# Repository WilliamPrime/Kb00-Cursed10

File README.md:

This was a shortish project where i wanted to make my own keyboard with my own layout.

The reason for wanting to do this was that i have limited desk space so i prefer a smaller more compact keyboard, so as of currently i use a 65% keyboard
however i do miss having a full size num pad and FN keys so i wanted to create a layout, and keyboard that would focus on getting a full key layout but making it more compact

# some pictures of the project

# BOM

|part    |cost  |notes               |link                                                 |
|--------|------|--------------------|-----------------------------------------------------|
|keycaps |19.97 |                    |https://www.aliexpress.com/item/1005005981079053.html|
|PCB     |43    |JLC!                |                                                     |
|Switches|34.19 |clicky clicky!      |https://www.aliexpress.com/item/1005007779640100.html|
|Diodes  |3.1   |need 2 lots of 1.55 |https://www.aliexpress.com/item/1005006127068810.html|
|PI pico |2.17  |pico with usb type c|https://www.aliexpress.com/item/1005003753933847.html|
|PLA     |0     |using my own        |                                                     |
|Sum     |111.61|                    |                                                     |

total cost $102.43

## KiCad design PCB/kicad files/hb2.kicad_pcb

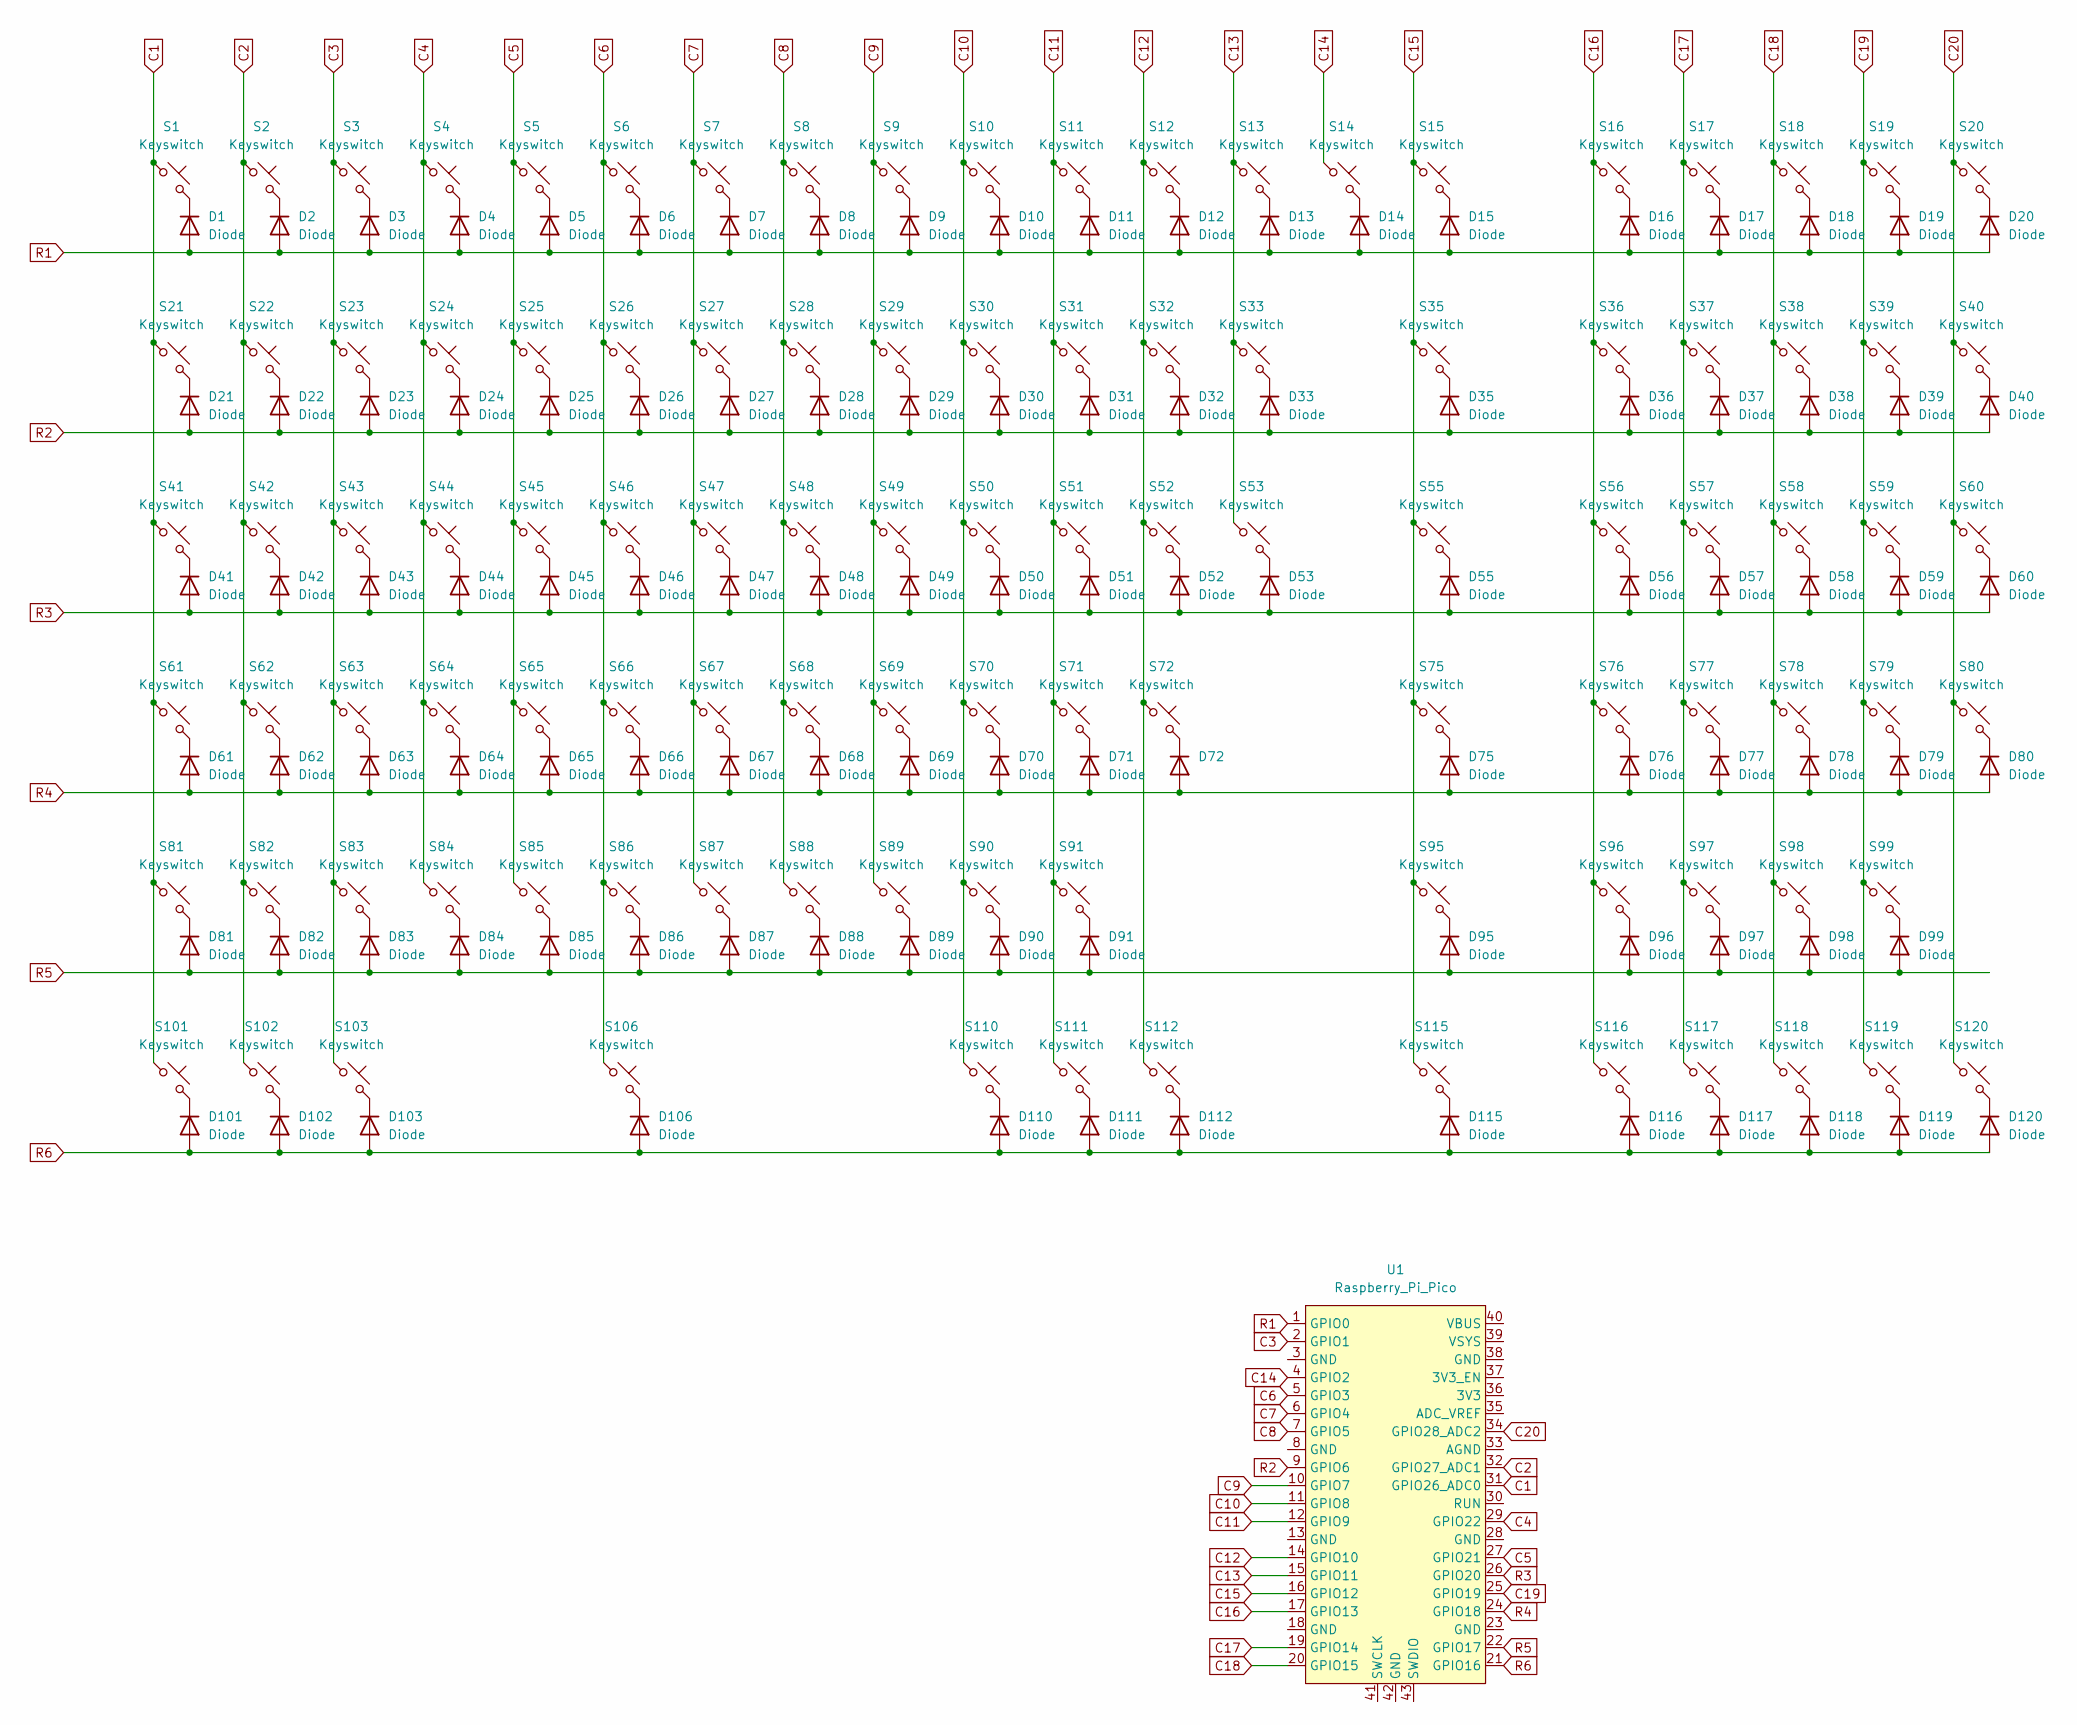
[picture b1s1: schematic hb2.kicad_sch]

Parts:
D1, D2, D3, D4, D5, D6, D7, D8, D9, D10, D11, D12, D13, D14, D15, D16, D17, D18, D19, D20, D21, D22, D23, D24, D25, D26, D27, D28, D29, D30, D31, D32, D33, D35, D36, D37, D38, D39, D40, D41, D42, D43, D44, D45, D46, D47, D48, D49, D50, D51, D52, D53, D55, D56, D57, D58, D59, D60, D61, D62, D63, D64, D65, D66, D67, D68, D69, D70, D71, D72, D75, D76, D77, D78, D79, D80, D81, D82, D83, D84, D85, D86, D87, D88, D89, D90, D91, D95, D96, D97, D98, D99, D101, D102, D103, D106, D110, D111, D112, D115, D116, D117, D118, D119, D120: Diode; D_DO-35_SOD27_P7.62mm_Horizontal
S1, S2, S3, S4, S5, S6, S7, S8, S9, S10, S11, S12, S13, S14, S15, S16, S17, S18, S19, S20, S21, S22, S23, S24, S25, S26, S27, S28, S29, S30, S31, S32, S33, S35, S36, S37, S38, S39, S40, S41, S42, S43, S44, S45, S46, S47, S48, S49, S50, S51, S52, S53, S55, S56, S57, S58, S59, S60, S61, S62, S63, S64, S65, S66, S67, S68, S69, S70, S71, S72, S75, S76, S77, S78, S79, S80, S81, S82, S83, S84, S85, S86, S87, S88, S89, S90, S91, S95, S96, S97, S98, S99, S101, S102, S103, S106, S110, S111, S112, S115, S116, S117, S118, S119, S120: Keyswitch; SW_Cherry_MX_PCB_1.00u
U1: Raspberry_Pi_Pico

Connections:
C1: S1.1, S21.1, S41.1, S61.1, S81.1, S101.1, U1.31 (GPIO26_ADC0)
C2: S2.1, S22.1, S42.1, S62.1, S82.1, S102.1, U1.32 (GPIO27_ADC1)
C3: S3.1, S23.1, S43.1, S63.1, S83.1, S103.1, U1.2 (GPIO1)
C4: S4.1, S24.1, S44.1, S64.1, S84.1, U1.29 (GPIO22)
C5: S5.1, S25.1, S45.1, S65.1, S85.1, U1.27 (GPIO21)
C6: S6.1, S26.1, S46.1, S66.1, S86.1, S106.1, U1.5 (GPIO3)
C7: S7.1, S27.1, S47.1, S67.1, S87.1, U1.6 (GPIO4)
C8: S8.1, S28.1, S48.1, S68.1, S88.1, U1.7 (GPIO5)
C9: S9.1, S29.1, S49.1, S69.1, S89.1, U1.10 (GPIO7)
C10: S10.1, S30.1, S50.1, S70.1, S90.1, S110.1, U1.11 (GPIO8)
C11: S11.1, S31.1, S51.1, S71.1, S91.1, S111.1, U1.12 (GPIO9)
C12: S12.1, S32.1, S52.1, S72.1, S112.1, U1.14 (GPIO10)
C13: S13.1, S33.1, S53.1, U1.15 (GPIO11)
C14: S14.1, U1.4 (GPIO2)
C15: S15.1, S35.1, S55.1, S75.1, S95.1, S115.1, U1.16 (GPIO12)
C16: S16.1, S36.1, S56.1, S76.1, S96.1, S116.1, U1.17 (GPIO13)
C17: S17.1, S37.1, S57.1, S77.1, S97.1, S117.1, U1.19 (GPIO14)
C18: S18.1, S38.1, S58.1, S78.1, S98.1, S118.1, U1.20 (GPIO15)
C19: S19.1, S39.1, S59.1, S79.1, S99.1, S119.1, U1.25 (GPIO19)
C20: S20.1, S40.1, S60.1, S80.1, S120.1, U1.34 (GPIO28_ADC2)
unnamed: D1.1 (K), S1.2
unnamed: D2.1 (K), S2.2
unnamed: D3.1 (K), S3.2
unnamed: D4.1 (K), S4.2
unnamed: D5.1 (K), S5.2
unnamed: D6.1 (K), S6.2
unnamed: D7.1 (K), S7.2
unnamed: D8.1 (K), S8.2
unnamed: D9.1 (K), S9.2
unnamed: D10.1 (K), S10.2
unnamed: D11.1 (K), S11.2
unnamed: D12.1 (K), S12.2
unnamed: D13.1 (K), S13.2
unnamed: D14.1 (K), S14.2
unnamed: D15.1 (K), S15.2
unnamed: D16.1 (K), S16.2
unnamed: D17.1 (K), S17.2
unnamed: D18.1 (K), S18.2
unnamed: D19.1 (K), S19.2
unnamed: D20.1 (K), S20.2
unnamed: D21.1 (K), S21.2
unnamed: D22.1 (K), S22.2
unnamed: D23.1 (K), S23.2
unnamed: D24.1 (K), S24.2
unnamed: D25.1 (K), S25.2
unnamed: D26.1 (K), S26.2
unnamed: D27.1 (K), S27.2
unnamed: D28.1 (K), S28.2
unnamed: D29.1 (K), S29.2
unnamed: D30.1 (K), S30.2
unnamed: D31.1 (K), S31.2
unnamed: D32.1 (K), S32.2
unnamed: D33.1 (K), S33.2
unnamed: D35.1 (K), S35.2
unnamed: D36.1 (K), S36.2
unnamed: D37.1 (K), S37.2
unnamed: D38.1 (K), S38.2
unnamed: D39.1 (K), S39.2
unnamed: D40.1 (K), S40.2
unnamed: D41.1 (K), S41.2
unnamed: D42.1 (K), S42.2
unnamed: D43.1 (K), S43.2
unnamed: D44.1 (K), S44.2
unnamed: D45.1 (K), S45.2
unnamed: D46.1 (K), S46.2
unnamed: D47.1 (K), S47.2
unnamed: D48.1 (K), S48.2
unnamed: D49.1 (K), S49.2
unnamed: D50.1 (K), S50.2
unnamed: D51.1 (K), S51.2
unnamed: D52.1 (K), S52.2
unnamed: D53.1 (K), S53.2
unnamed: D55.1 (K), S55.2
unnamed: D56.1 (K), S56.2
unnamed: D57.1 (K), S57.2
unnamed: D58.1 (K), S58.2
unnamed: D59.1 (K), S59.2
unnamed: D60.1 (K), S60.2
unnamed: D61.1 (K), S61.2
unnamed: D62.1 (K), S62.2
unnamed: D63.1 (K), S63.2
unnamed: D64.1 (K), S64.2
unnamed: D65.1 (K), S65.2
unnamed: D66.1 (K), S66.2
unnamed: D67.1 (K), S67.2
unnamed: D68.1 (K), S68.2
unnamed: D69.1 (K), S69.2
unnamed: D70.1 (K), S70.2
unnamed: D71.1 (K), S71.2
unnamed: D72.1 (K), S72.2
unnamed: D75.1 (K), S75.2
unnamed: D76.1 (K), S76.2
unnamed: D77.1 (K), S77.2
unnamed: D78.1 (K), S78.2
unnamed: D79.1 (K), S79.2
unnamed: D80.1 (K), S80.2
unnamed: D81.1 (K), S81.2
unnamed: D82.1 (K), S82.2
unnamed: D83.1 (K), S83.2
unnamed: D84.1 (K), S84.2
unnamed: D85.1 (K), S85.2
unnamed: D86.1 (K), S86.2
unnamed: D87.1 (K), S87.2
unnamed: D88.1 (K), S88.2
unnamed: D89.1 (K), S89.2
unnamed: D90.1 (K), S90.2
unnamed: D91.1 (K), S91.2
unnamed: D95.1 (K), S95.2
unnamed: D96.1 (K), S96.2
unnamed: D97.1 (K), S97.2
unnamed: D98.1 (K), S98.2
unnamed: D99.1 (K), S99.2
unnamed: D101.1 (K), S101.2
unnamed: D102.1 (K), S102.2
unnamed: D103.1 (K), S103.2
unnamed: D106.1 (K), S106.2
unnamed: D110.1 (K), S110.2
unnamed: D111.1 (K), S111.2
unnamed: D112.1 (K), S112.2
unnamed: D115.1 (K), S115.2
unnamed: D116.1 (K), S116.2
unnamed: D117.1 (K), S117.2
unnamed: D118.1 (K), S118.2
unnamed: D119.1 (K), S119.2
unnamed: D120.1 (K), S120.2
R1: D1.2 (A), D2.2 (A), D3.2 (A), D4.2 (A), D5.2 (A), D6.2 (A), D7.2 (A), D8.2 (A), D9.2 (A), D10.2 (A), D11.2 (A), D12.2 (A), D13.2 (A), D14.2 (A), D15.2 (A), D16.2 (A), D17.2 (A), D18.2 (A), D19.2 (A), D20.2 (A), U1.1 (GPIO0)
R2: D21.2 (A), D22.2 (A), D23.2 (A), D24.2 (A), D25.2 (A), D26.2 (A), D27.2 (A), D28.2 (A), D29.2 (A), D30.2 (A), D31.2 (A), D32.2 (A), D33.2 (A), D35.2 (A), D36.2 (A), D37.2 (A), D38.2 (A), D39.2 (A), D40.2 (A), U1.9 (GPIO6)
R3: D41.2 (A), D42.2 (A), D43.2 (A), D44.2 (A), D45.2 (A), D46.2 (A), D47.2 (A), D48.2 (A), D49.2 (A), D50.2 (A), D51.2 (A), D52.2 (A), D53.2 (A), D55.2 (A), D56.2 (A), D57.2 (A), D58.2 (A), D59.2 (A), D60.2 (A), U1.26 (GPIO20)
R4: D61.2 (A), D62.2 (A), D63.2 (A), D64.2 (A), D65.2 (A), D66.2 (A), D67.2 (A), D68.2 (A), D69.2 (A), D70.2 (A), D71.2 (A), D72.2 (A), D75.2 (A), D76.2 (A), D77.2 (A), D78.2 (A), D79.2 (A), D80.2 (A), U1.24 (GPIO18)
R5: D81.2 (A), D82.2 (A), D83.2 (A), D84.2 (A), D85.2 (A), D86.2 (A), D87.2 (A), D88.2 (A), D89.2 (A), D90.2 (A), D91.2 (A), D95.2 (A), D96.2 (A), D97.2 (A), D98.2 (A), D99.2 (A), U1.22 (GPIO17)
R6: D101.2 (A), D102.2 (A), D103.2 (A), D106.2 (A), D110.2 (A), D111.2 (A), D112.2 (A), D115.2 (A), D116.2 (A), D117.2 (A), D118.2 (A), D119.2 (A), D120.2 (A), U1.21 (GPIO16)

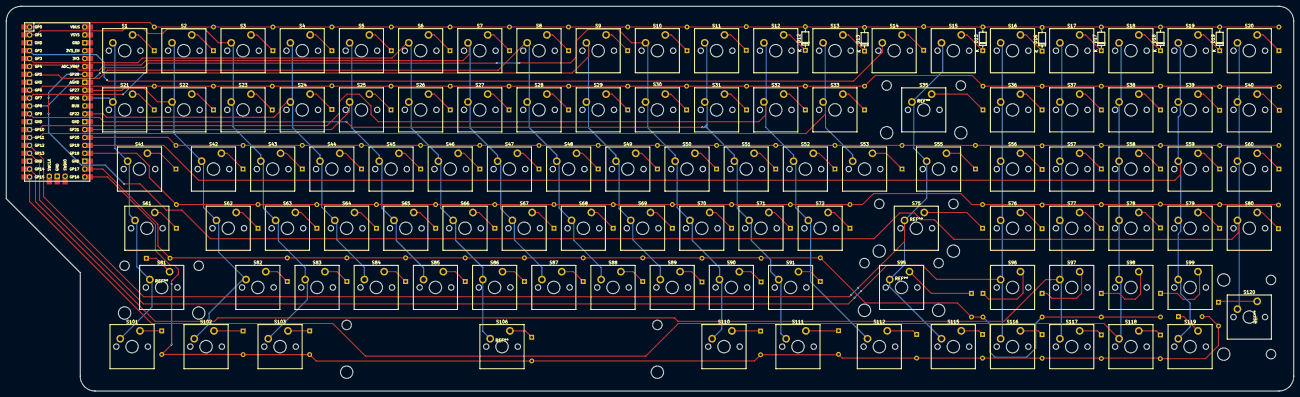
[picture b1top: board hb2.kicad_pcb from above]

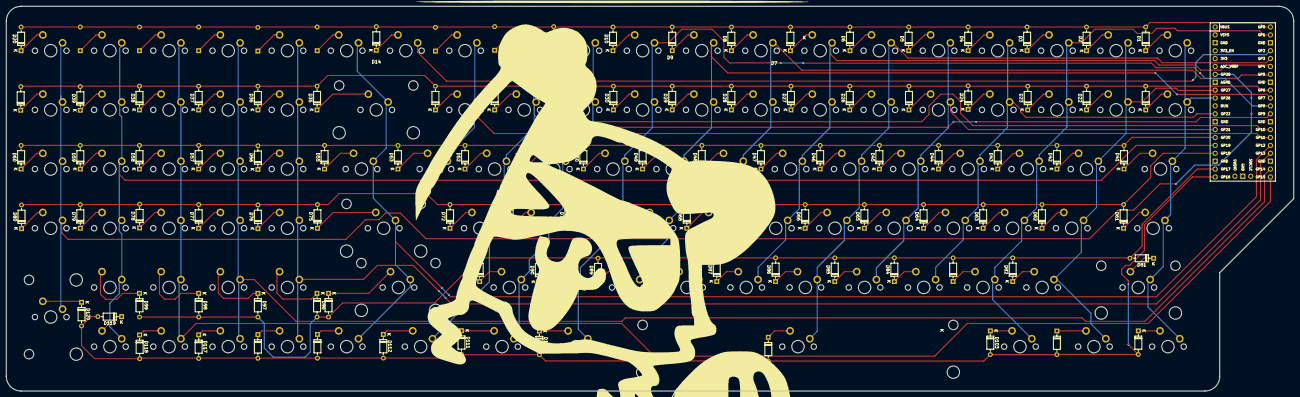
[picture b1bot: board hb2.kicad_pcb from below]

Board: 2 copper layers, 414.3 x 123.8 mm, 211 parts (98 on the bottom side), 131 nets.

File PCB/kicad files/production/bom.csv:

Designator,Footprint,Quantity,Value,LCSC Part #
"D1, D10, D101, D102, D103, D106, D11, D110, D111, D112, D115, D116, D117, D118, D119, D12, D120, D13, D14, D15, D16, D17, D18, D19, D2, D20, D21, D22, D23, D24, D25, D26, D27, D28, D29, D3, D30, D31, D32, D33, D35, D36, D37, D38, D39, D4, D40, D41, D42, D43, D44, D45, D46, D47, D48, D49, D5, D50, D51, D52, D53, D55, D56, D57, D58, D59, D6, D60, D61, D62, D63, D64, D65, D66, D67, D68, D69, D7, D70, D71, D72, D75, D76, D77, D78, D79, D8, D80, D81, D82, D83, D84, D85, D86, D87, D88, D89, D9, D90, D91, D95, D96, D97, D98, D99",D_DO-35_SOD27_P7.62mm_Horizontal,105,Diode,
"S1, S10, S101, S102, S103, S106, S11, S110, S111, S112, S115, S116, S117, S118, S119, S12, S120, S13, S14, S15, S16, S17, S18, S19, S2, S20, S21, S22, S23, S24, S25, S26, S27, S28, S29, S3, S30, S31, S32, S33, S35, S36, S37, S38, S39, S4, S40, S41, S42, S43, S44, S45, S46, S47, S48, S49, S5, S50, S51, S52, S53, S55, S56, S57, S58, S59, S6, S60, S61, S62, S63, S64, S65, S66, S67, S68, S69, S7, S70, S71, S72, S75, S76, S77, S78, S79, S8, S80, S81, S82, S83, S84, S85, S86, S87, S88, S89, S9, S90, S91, S95, S96, S97, S98, S99",SW_Cherry_MX_PCB_1.00u,105,Keyswitch,
U1,Raspberry_Pi_Pico,1,Raspberry_Pi_Pico,

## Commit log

2025-07-19 added BOM
2025-07-19 Acutally adding the CAD and PCB
    actually added what i meant to add the first time
2025-07-19 added firmware
    firmware files
2025-07-19 updated bom to indclude solder
    updated bom to inc solder
    also the prices keep changing :pf:
2025-08-07 just some imgs
2025-08-14 Update journal.md
    added the build thing
2026-01-20 Correct total cost in the parts list
    Updated total cost in the README file.
